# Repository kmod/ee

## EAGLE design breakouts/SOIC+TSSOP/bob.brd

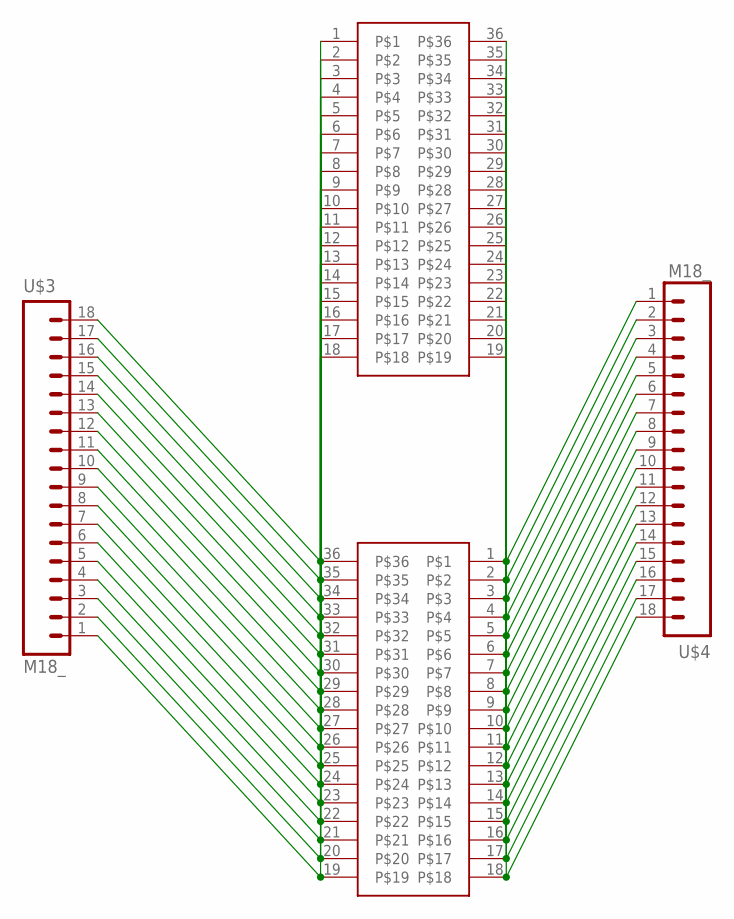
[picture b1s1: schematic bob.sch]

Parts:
U$1: 36PIN_BREAKOUTSOIC; SOIC-8-36-BREAKOUT
U$2: 36PIN_BREAKOUTTSSOP; TSSOP-8-36-BREAKOUT
U$3, U$4: M18_; 1X18

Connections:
unnamed: U$1.17, U$2.20, U$3.2
unnamed: U$1.16, U$2.21, U$3.3
unnamed: U$1.15, U$2.22, U$3.4
unnamed: U$1.14, U$2.23, U$3.5
unnamed: U$1.13, U$2.24, U$3.6
unnamed: U$1.12, U$2.25, U$3.7
unnamed: U$1.11, U$2.26, U$3.8
unnamed: U$1.10, U$2.27, U$3.9
unnamed: U$1.9, U$2.28, U$3.10
unnamed: U$1.8, U$2.29, U$3.11
unnamed: U$1.7, U$2.30, U$3.12
unnamed: U$1.6, U$2.31, U$3.13
unnamed: U$1.5, U$2.32, U$3.14
unnamed: U$1.4, U$2.33, U$3.15
unnamed: U$1.3, U$2.34, U$3.16
unnamed: U$1.2, U$2.35, U$3.17
unnamed: U$1.1, U$2.36, U$3.18
unnamed: U$1.18, U$2.19, U$3.1
unnamed: U$1.35, U$2.2, U$4.2
unnamed: U$1.34, U$2.3, U$4.3
unnamed: U$1.33, U$2.4, U$4.4
unnamed: U$1.32, U$2.5, U$4.5
unnamed: U$1.31, U$2.6, U$4.6
unnamed: U$1.30, U$2.7, U$4.7
unnamed: U$1.29, U$2.8, U$4.8
unnamed: U$1.28, U$2.9, U$4.9
unnamed: U$1.27, U$2.10, U$4.10
unnamed: U$1.26, U$2.11, U$4.11
unnamed: U$1.25, U$2.12, U$4.12
unnamed: U$1.24, U$2.13, U$4.13
unnamed: U$1.23, U$2.14, U$4.14
unnamed: U$1.22, U$2.15, U$4.15
unnamed: U$1.21, U$2.16, U$4.16
unnamed: U$1.20, U$2.17, U$4.17
unnamed: U$1.19, U$2.18, U$4.18
unnamed: U$1.36, U$2.1, U$4.1

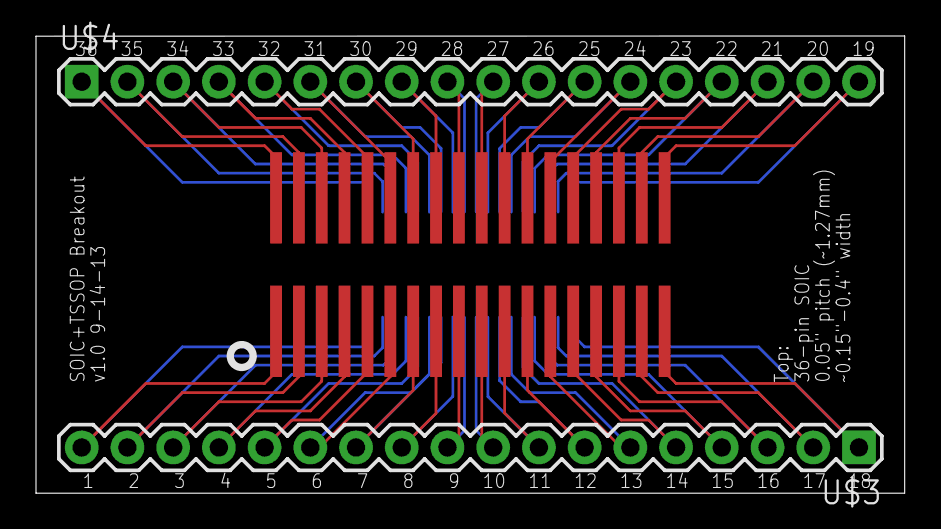
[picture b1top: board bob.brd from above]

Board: 4 copper layers, 48.3 x 25.4 mm, 4 parts (1 on the bottom side), 36 nets.

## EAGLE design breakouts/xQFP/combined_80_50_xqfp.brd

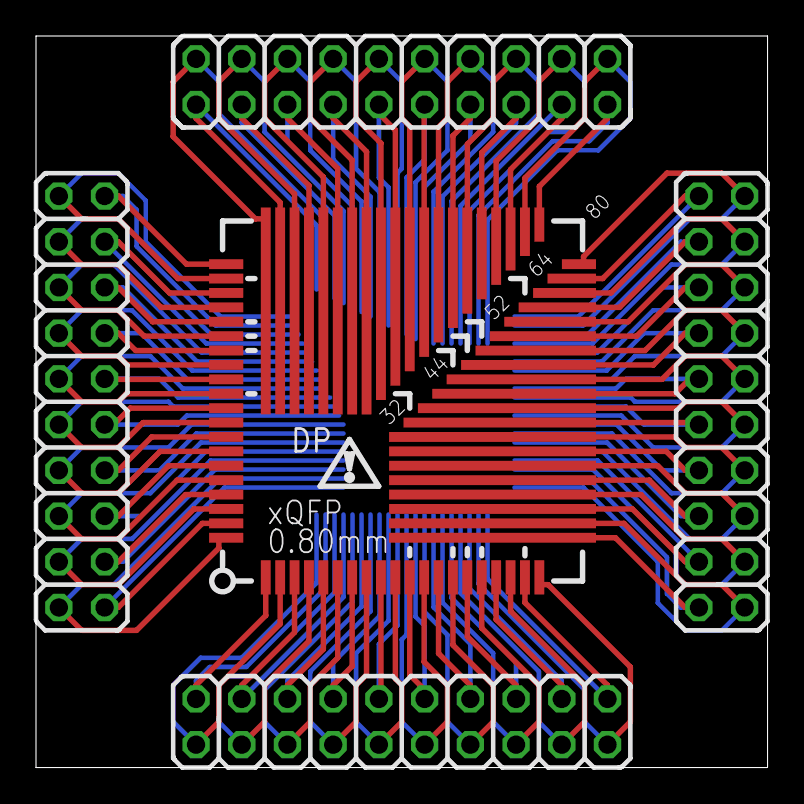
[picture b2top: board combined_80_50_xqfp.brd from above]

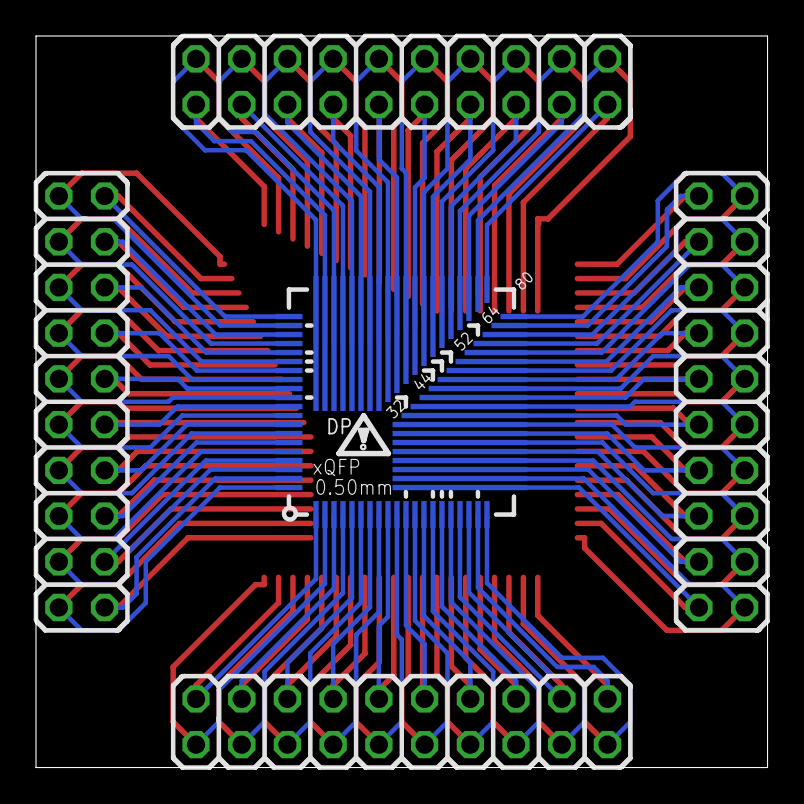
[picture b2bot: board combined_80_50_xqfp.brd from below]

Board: 4 copper layers, 40.6 x 40.6 mm, 6 parts (5 on the bottom side), 80 nets.

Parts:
JP13, JP14, JP15, JP16: 2X10
U$1: BB_XQFP_050; BB_QFP_050
U$2: BB_XQFP_080; BB_QFP_080

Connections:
unnamed: JP13.1, U$2.1
unnamed: JP13.2, U$2.2
unnamed: JP13.3, U$2.3
unnamed: JP13.4, U$2.4
unnamed: JP13.5, U$2.5
unnamed: JP13.6, U$2.6
unnamed: JP13.7, U$2.7
unnamed: JP13.8, U$2.8
unnamed: JP13.9, U$2.9
unnamed: JP13.10, U$2.10
unnamed: JP13.11, U$2.11
unnamed: JP13.12, U$2.12
unnamed: JP13.13, U$2.13
unnamed: JP13.14, U$2.14
unnamed: JP13.15, U$2.15
unnamed: JP13.16, U$2.16
unnamed: JP13.17, U$2.17
unnamed: JP13.18, U$2.18
unnamed: JP13.19, U$2.19
unnamed: JP13.20, U$2.20
unnamed: JP14.1, U$2.21
unnamed: JP14.2, U$2.22
unnamed: JP14.3, U$2.23
unnamed: JP14.4, U$2.24
unnamed: JP14.5, U$2.25
unnamed: JP14.6, U$2.26
unnamed: JP14.7, U$2.27
unnamed: JP14.8, U$2.28
unnamed: JP14.9, U$2.29
unnamed: JP14.10, U$2.30
unnamed: JP14.11, U$2.31
unnamed: JP14.12, U$2.32
unnamed: JP14.13, U$2.33
unnamed: JP14.14, U$2.34
unnamed: JP14.15, U$2.35
unnamed: JP14.16, U$2.36
unnamed: JP14.17, U$2.37
unnamed: JP14.18, U$2.38
unnamed: JP14.19, U$2.39
unnamed: JP14.20, U$2.40
unnamed: JP15.1, U$2.41
unnamed: JP15.2, U$2.42
unnamed: JP15.3, U$2.43
unnamed: JP15.4, U$2.44
unnamed: JP15.5, U$2.45
unnamed: JP15.6, U$2.46
unnamed: JP15.7, U$2.47
unnamed: JP15.8, U$2.48
unnamed: JP15.9, U$2.49
unnamed: JP15.10, U$2.50
unnamed: JP15.11, U$2.51
unnamed: JP15.12, U$2.52
unnamed: JP15.13, U$2.53
unnamed: JP15.14, U$2.54
unnamed: JP15.15, U$2.55
unnamed: JP15.16, U$2.56
unnamed: JP15.17, U$2.57
unnamed: JP15.18, U$2.58
unnamed: JP15.19, U$2.59
unnamed: JP15.20, U$2.60
unnamed: JP16.1, U$2.61
unnamed: JP16.2, U$2.62
unnamed: JP16.3, U$2.63
unnamed: JP16.4, U$2.64
unnamed: JP16.5, U$2.65
unnamed: JP16.6, U$2.66
unnamed: JP16.7, U$2.67
unnamed: JP16.8, U$2.68
unnamed: JP16.9, U$2.69
unnamed: JP16.10, U$2.70
unnamed: JP16.11, U$2.71
unnamed: JP16.12, U$2.72
unnamed: JP16.13, U$2.73
unnamed: JP16.14, U$2.74
unnamed: JP16.15, U$2.75
unnamed: JP16.16, U$2.76
unnamed: JP16.17, U$2.77
unnamed: JP16.18, U$2.78
unnamed: JP16.19, U$2.79
unnamed: JP16.20, U$2.80

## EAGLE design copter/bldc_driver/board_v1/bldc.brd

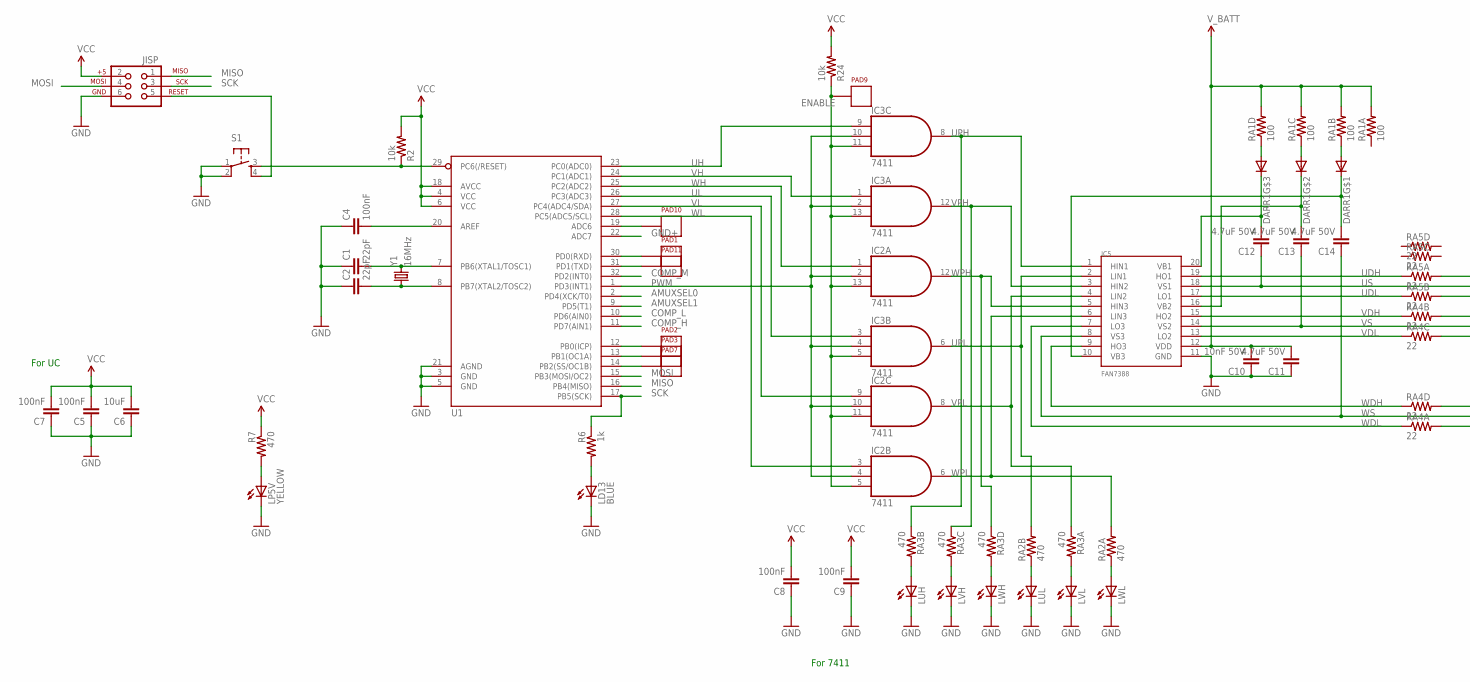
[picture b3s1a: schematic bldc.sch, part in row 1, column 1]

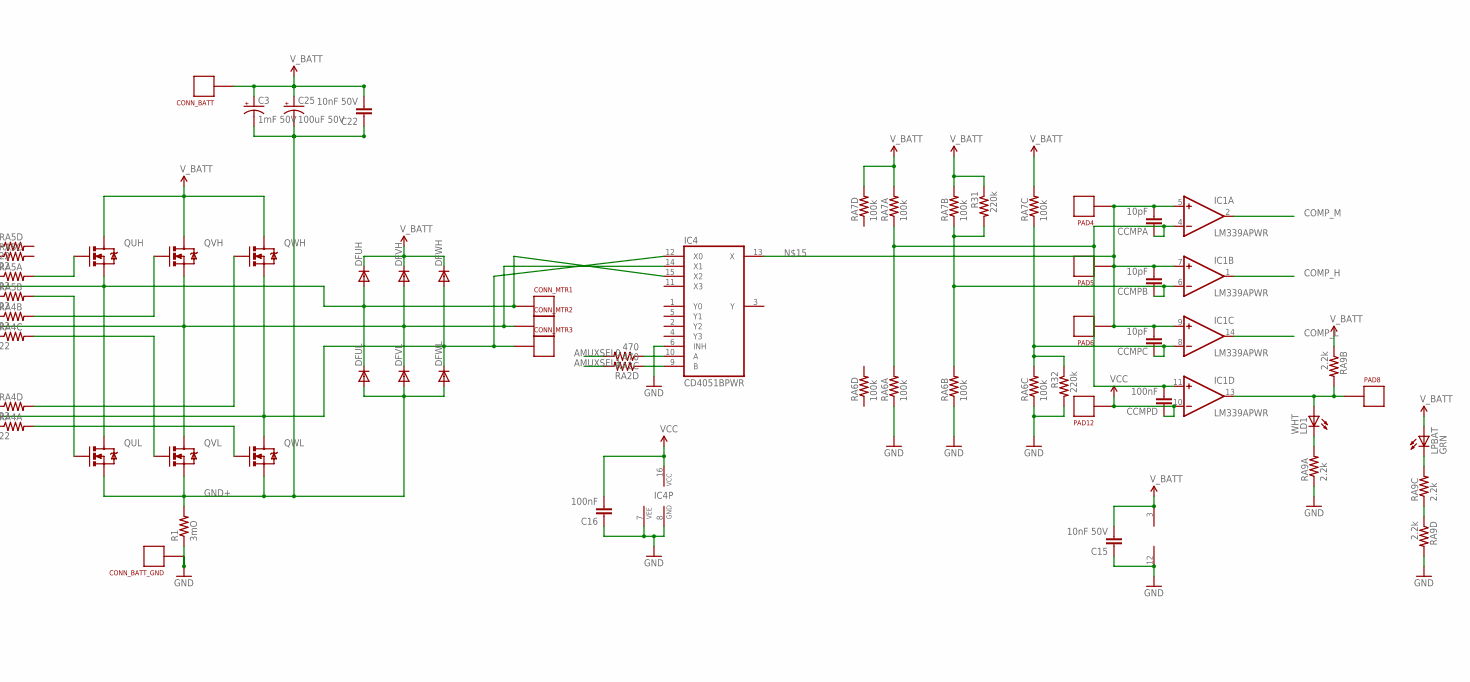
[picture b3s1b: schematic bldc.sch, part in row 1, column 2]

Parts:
C1, C2: 22pF; 0402-CAP
C3: 1mF 50V; CPOL-RADIAL-1000UF-50V
C4, C5, C7, C8, C9, C16: 100nF; 0402-CAP
C6: 10uF; 0805
C10, C15, C22: 10nF 50V; 0402-CAP
C11: 4.7uF 50V; 0805
C12, C13, C14: 4.7uF 50V; 0805; VOLTAGE 40
C25: 100uF 50V; CPOL-RADIAL-100UF-25V
CCMPA: 10pF; 0402-CAP
CCMPB: 10pF; 0402-CAP
CCMPC: 10pF; 0402-CAP
CCMPD: 100nF; 0402-CAP
CONN_BATT: CONNECTOR18AWG; HOLE_18AWG
CONN_BATT_GND: CONNECTOR18AWG; HOLE_18AWG
CONN_MTR1, CONN_MTR2, CONN_MTR3: CONNECTOR18AWG; HOLE_18AWG
DARR1: SD103ATW-7-F; SOT363
DFUH: DIODESOD123W; SOD123W(NXP)
DFUL: DIODESOD123W; SOD123W(NXP)
DFVH: DIODESOD123W; SOD123W(NXP)
DFVL: DIODESOD123W; SOD123W(NXP)
DFWH: DIODESOD123W; SOD123W(NXP)
DFWL: DIODESOD123W; SOD123W(NXP)
IC1: LM339APWR; TSSOP14
IC2, IC3: 7411; TSSOP14
IC4: CD4051BPWR; TSSOP16
IC5: FAN7388; SO20W
JISP: AVR_SPI_PRG_6PTH; 2X3
LD1: WHT; 0603_LED
LD13: BLUE; 0603_LED
LP5V: YELLOW; 0603_LED
LPBAT: GRN; 0603_LED
LUH: LED0603; 0603_LED
LUL: LED0603; 0603_LED
LVH: LED0603; 0603_LED
LVL: LED0603; 0603_LED
LWH: LED0603; 0603_LED
LWL: LED0603; 0603_LED
PAD1: PD0; TESTPAD
PAD2: PB0; TESTPAD
PAD3: PB1; TESTPAD
PAD4: CMPA; TESTPAD
PAD5: CMPB; TESTPAD
PAD6: CMPC; TESTPAD
PAD7: PB2; TESTPAD
PAD8: PGD; TESTPAD
PAD9: ENBL; TESTPAD
PAD10: ADC6; TESTPAD
PAD11: PD1; TESTPAD
PAD12: VREF; TESTPAD
QUH: NXP_LFPAK_NFET; POWERSO8
QUL: NXP_LFPAK_NFET; POWERSO8
QVH: NXP_LFPAK_NFET; POWERSO8
QVL: NXP_LFPAK_NFET; POWERSO8
QWH: NXP_LFPAK_NFET; POWERSO8
QWL: NXP_LFPAK_NFET; POWERSO8
R1: 3mO; OAR5
R2, R24: 10k; 0603-RES
R6: 1k; 0603-RES
R7: 470; 0603-RES
R31, R32: 220k; 0603-RES
RA1: 100; 0603-ARV
RA2, RA3: 470; 0603-ARV
RA4, RA5: 22; 0603-ARV
RA6, RA7: 100k; 0603-ARV
RA9: 2.2k; 0603-ARV
S1: TAC_SWITCHPTH; TACTILE-PTH
U1: ATMEGA328_SMT; TQFP32-08
Y1: 16MHz; HC49UP

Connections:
AMUXSEL0: RA2.6 (2), U1.2 (PD4(XCK/T0))
AMUXSEL1: RA2.5 (2), U1.9 (PD5(T1))
COMP_H: IC1.1 (OUT), U1.11 (PD7(AIN1))
COMP_L: IC1.14 (OUT), U1.10 (PD6(AIN0))
COMP_M: IC1.2 (OUT), U1.32 (PD2(INT0))
CTL0: PAD2.P, U1.12 (PB0(ICP))
CTL1: PAD3.P, U1.13 (PB1(OC1A))
CTL2: PAD7.P, U1.14 (PB2(SS/OC1B))
CTL3: PAD1.P, U1.30 (PD0(RXD))
ENABLE: IC2.5 (I2), IC2.11 (I2), IC2.13 (I2), IC3.5 (I2), IC3.11 (I2), IC3.13 (I2), PAD9.P, R24.1
GND: C1.1, C2.1, C4.1, C5.1, C6.1, C7.1, C8.1, C9.1, C10.1, C11.1, C15.1, C16.1, CONN_BATT_GND.P$1, IC1.12 (GND), IC2.7 (GND), IC3.7 (GND), IC4.6 (INH), IC4.7 (VEE), IC4.8 (GND), IC5.11 (GND), JISP.6, LD13.C, LP5V.C, LUH.C, LUL.C, LVH.C, LVL.C, LWH.C, LWL.C, R1.P$1 (1), R32.2, RA6.1, RA6.2 (1), RA6.3 (1), RA9.1, RA9.5 (2), S1.1, S1.2, U1.3 (GND), U1.5 (GND), U1.21 (AGND)
GND+: C3.2 (-), C22.1, C25.2 (-), DFUL.A, DFVL.A, DFWL.A, QUL.P1 (S), QUL.P2 (S), QUL.P3 (S), QVL.P1 (S), QVL.P2 (S), QVL.P3 (S), QWL.P1 (S), QWL.P2 (S), QWL.P3 (S), R1.P$2 (2), U1.22 (ADC7)
GUH: QUH.P4 (G), RA5.8 (2)
GUL: QUL.P4 (G), RA5.7 (2)
GVH: QVH.P4 (G), RA4.7 (2)
GVL: QVL.P4 (G), RA4.6 (2)
GWH: QWH.P4 (G), RA4.5 (2)
GWL: QWL.P4 (G), RA4.8 (2)
MISO: JISP.1, U1.16 (PB4(MISO))
MOSI: JISP.4, U1.15 (PB3(MOSI/OC2))
unnamed: C1.2, U1.7 (PB6(XTAL1/TOSC1)), Y1.2
unnamed: C2.2, U1.8 (PB7(XTAL2/TOSC2)), Y1.1
unnamed: CCMPA.1, CCMPD.2, IC1.4 (-IN), IC1.11 (+IN), RA6.8 (2), RA7.1
unnamed: IC1.13 (OUT), LD1.A, PAD8.P, RA9.7 (2)
unnamed: C4.2, U1.20 (AREF)
unnamed: LD13.A, R6.2
unnamed: RA9.3 (1), RA9.4 (1)
unnamed: LUH.A, RA3.7 (2)
unnamed: LWL.A, RA2.1
unnamed: LP5V.A, R7.2
unnamed: CCMPB.1, IC1.6 (-IN), R31.2, RA6.7 (2), RA7.2 (1)
unnamed: IC4.10 (A), RA2.3 (1)
unnamed: LD1.C, RA9.8 (2)
unnamed: IC4.9 (B), RA2.4 (1)
unnamed: CCMPA.2, CCMPB.2, CCMPC.2, IC1.5 (+IN), IC1.7 (+IN), IC1.9 (+IN), IC4.13 (X), PAD4.P, PAD5.P, PAD6.P
unnamed: LPBAT.C, RA9.6 (2)
unnamed: CCMPC.1, IC1.8 (-IN), R32.1, RA6.6 (2), RA7.3 (1)
unnamed: C14.2, DARR1.1 (C), IC5.10 (VB3)
unnamed: DARR1.4 (A), RA1.4 (1)
unnamed: DARR1.5 (A), RA1.3 (1)
unnamed: DARR1.6 (A), RA1.2 (1)
unnamed: JISP.5, S1.4
unnamed: LVH.A, RA3.6 (2)
unnamed: LWH.A, RA3.5 (2)
unnamed: LUL.A, RA2.2 (1)
unnamed: PAD10.P, U1.19 (ADC6)
unnamed: PAD11.P, U1.31 (PD1(TXD))
unnamed: C13.2, DARR1.2 (C), IC5.16 (VB2)
unnamed: C12.2, DARR1.3 (C), IC5.20 (VB1)
unnamed: LVL.A, RA3.8 (2)
PWM: IC2.2 (I1), IC2.4 (I1), IC2.10 (I1), IC3.2 (I1), IC3.4 (I1), IC3.10 (I1), U1.1 (PD3(INT1))
RESET: R2.1, S1.3, U1.29 (PC6(/RESET))
SCK: JISP.3, R6.1, U1.17 (PB5(SCK))
UDH: IC5.19 (HO1), RA5.1
UDL: IC5.17 (LO1), RA5.2 (1)
UH: IC3.9 (I0), U1.23 (PC0(ADC0))
UL: IC3.3 (I0), U1.26 (PC3(ADC3))
UPH: IC3.8 (O), IC5.1 (HIN1), RA3.2 (1)
UPL: IC3.6 (O), IC5.2 (LIN1), RA2.7 (2)
US: C12.1, CONN_MTR1.P$1, DFUH.A, DFUL.C, IC4.15 (X2), IC5.18 (VS1), QUH.P1 (S), QUH.P2 (S), QUH.P3 (S), QUL.P$1 (D), QUL.P$5 (D), QUL.P$6 (D), QUL.P$7 (D), QUL.P$8 (D), QUL.P$9 (D), QUL.P$10 (D), QUL.P$11 (D), QUL.P$12 (D), QUL.P$13 (D), QUL.P$14 (D), QUL.P$15 (D), QUL.P$16 (D), QUL.P$17 (D), QUL.P$19 (D), QUL.P$20 (D), QUL.P$21 (D)
VCC: C5.2, C6.2, C7.2, C8.2, C9.2, C16.2, CCMPD.1, IC1.10 (-IN), IC2.14 (VCC), IC3.14 (VCC), IC4.16 (VCC), JISP.2, PAD12.P, R2.2, R7.1, R24.2, U1.4 (VCC), U1.6 (VCC), U1.18 (AVCC)
VDH: IC5.15 (HO2), RA4.2 (1)
VDL: IC5.13 (LO2), RA4.3 (1)
VH: IC3.1 (I0), U1.24 (PC1(ADC1))
VL: IC2.9 (I0), U1.27 (PC4(ADC4/SDA))
VPH: IC3.12 (O), IC5.3 (HIN2), RA3.3 (1)
VPL: IC2.8 (O), IC5.4 (LIN2), RA3.1
VS: C13.1, CONN_MTR2.P$1, DFVH.A, DFVL.C, IC4.14 (X1), IC5.14 (VS2), QVH.P1 (S), QVH.P2 (S), QVH.P3 (S), QVL.P$1 (D), QVL.P$5 (D), QVL.P$6 (D), QVL.P$7 (D), QVL.P$8 (D), QVL.P$9 (D), QVL.P$10 (D), QVL.P$11 (D), QVL.P$12 (D), QVL.P$13 (D), QVL.P$14 (D), QVL.P$15 (D), QVL.P$16 (D), QVL.P$17 (D), QVL.P$19 (D), QVL.P$20 (D), QVL.P$21 (D)
V_BATT: C3.1 (+), C10.2, C11.2, C15.2, C22.2, C25.1 (+), CONN_BATT.P$1, DFUH.C, DFVH.C, DFWH.C, IC1.3 (V+), IC5.12 (VDD), LPBAT.A, QUH.P$1 (D), QUH.P$5 (D), QUH.P$6 (D), QUH.P$7 (D), QUH.P$8 (D), QUH.P$9 (D), QUH.P$10 (D), QUH.P$11 (D), QUH.P$12 (D), QUH.P$13 (D), QUH.P$14 (D), QUH.P$15 (D), QUH.P$16 (D), QUH.P$17 (D), QUH.P$19 (D), QUH.P$20 (D), QUH.P$21 (D), QVH.P$1 (D), QVH.P$5 (D), QVH.P$6 (D), QVH.P$7 (D), QVH.P$8 (D), QVH.P$9 (D), QVH.P$10 (D), QVH.P$11 (D), QVH.P$12 (D), QVH.P$13 (D), QVH.P$14 (D), QVH.P$15 (D), QVH.P$16 (D), QVH.P$17 (D), QVH.P$19 (D), QVH.P$20 (D), QVH.P$21 (D), QWH.P$1 (D), QWH.P$5 (D), QWH.P$6 (D), QWH.P$7 (D), QWH.P$8 (D), QWH.P$9 (D), QWH.P$10 (D), QWH.P$11 (D), QWH.P$12 (D), QWH.P$13 (D), QWH.P$14 (D), QWH.P$15 (D), QWH.P$16 (D), QWH.P$17 (D), QWH.P$19 (D), QWH.P$20 (D), QWH.P$21 (D), R31.1, RA1.5 (2), RA1.6 (2), RA1.7 (2), RA1.8 (2), RA7.5 (2), RA7.6 (2), RA7.7 (2), RA7.8 (2), RA9.2 (1)
WDH: IC5.9 (HO3), RA4.4 (1)
WDL: IC5.7 (LO3), RA4.1
WH: IC2.1 (I0), U1.25 (PC2(ADC2))
WL: IC2.3 (I0), U1.28 (PC5(ADC5/SCL))
WPH: IC2.12 (O), IC5.5 (HIN3), RA3.4 (1)
WPL: IC2.6 (O), IC5.6 (LIN3), RA2.8 (2)
WS: C14.1, CONN_MTR3.P$1, DFWH.A, DFWL.C, IC4.12 (X0), IC5.8 (VS3), QWH.P1 (S), QWH.P2 (S), QWH.P3 (S), QWL.P$1 (D), QWL.P$5 (D), QWL.P$6 (D), QWL.P$7 (D), QWL.P$8 (D), QWL.P$9 (D), QWL.P$10 (D), QWL.P$11 (D), QWL.P$12 (D), QWL.P$13 (D), QWL.P$14 (D), QWL.P$15 (D), QWL.P$16 (D), QWL.P$17 (D), QWL.P$19 (D), QWL.P$20 (D), QWL.P$21 (D)

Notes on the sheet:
For UC
For 7411

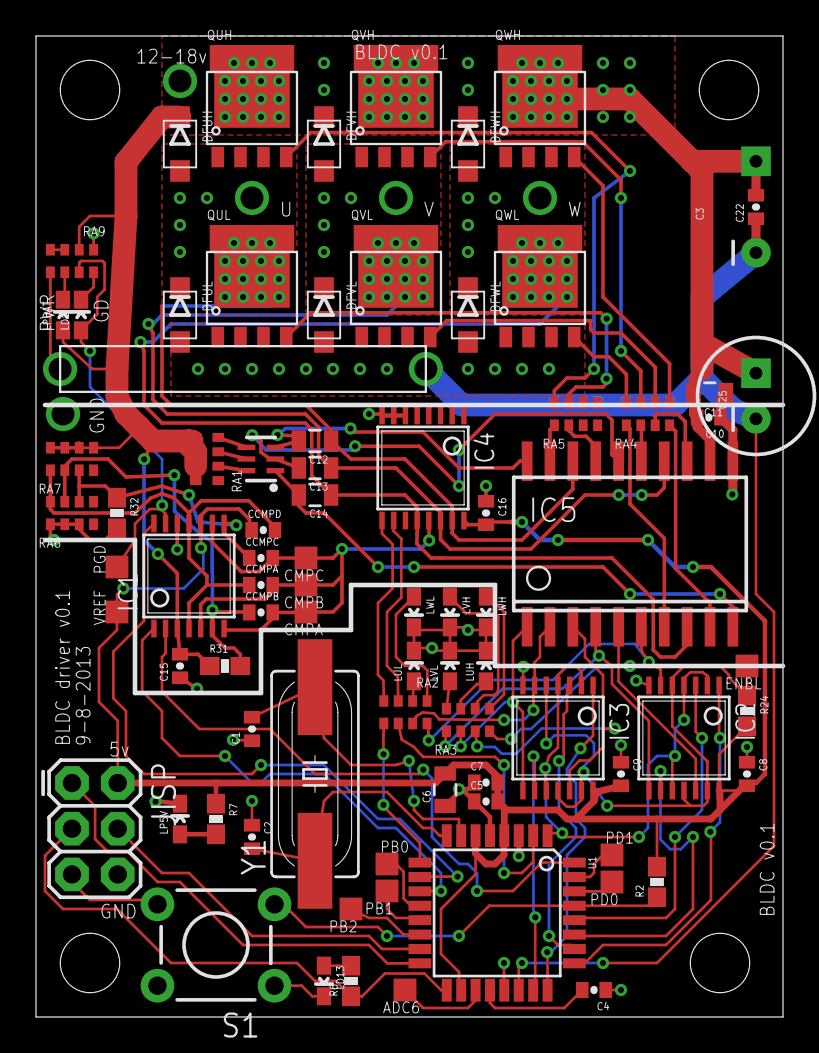
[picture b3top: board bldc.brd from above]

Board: 2 copper layers, 41.5 x 54.5 mm, 90 parts (0 on the bottom side), 76 nets.

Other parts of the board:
U$1, U$2, U$3, U$4: STAND-OFF

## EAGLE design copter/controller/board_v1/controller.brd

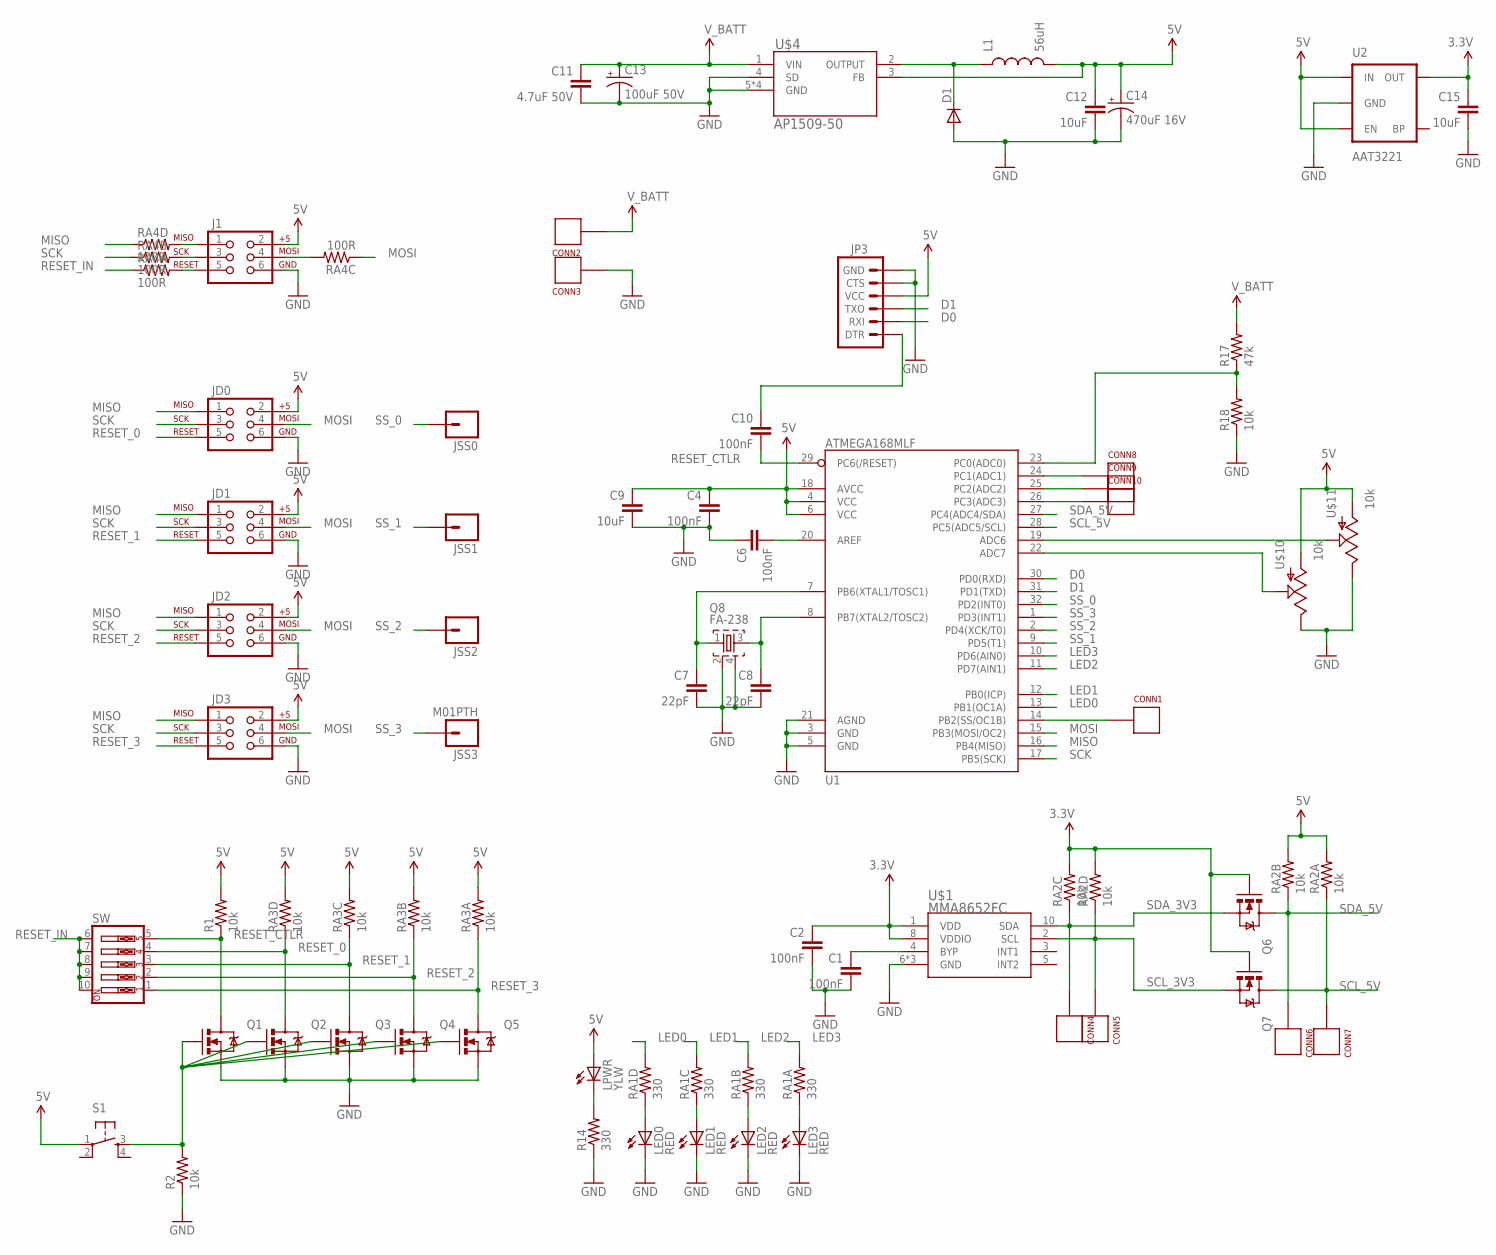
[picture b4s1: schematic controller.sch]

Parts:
C1, C2, C4, C6, C10: 100nF; 0402-CAP
C7, C8: 22pF; 0402-CAP
C9, C12, C15: 10uF; 0805
C11: 4.7uF 50V; 0805
C13: 100uF 50V; CAP-8-3.5
C14: 470uF 16V; CAP-8-3.5
CONN1: SS; TESTPAD
CONN2, CONN3: CONNECTOR18AWG; HOLE_18AWG
CONN4: D33; TESTPAD
CONN5: C33; TESTPAD
CONN6: D50; TESTPAD
CONN7: C50; TESTPAD
CONN8: PC1; TESTPAD
CONN9: PC2; TESTPAD
CONN10: PC3; TESTPAD
D1: DIODESOD123W; SOD123W(NXP)
J1: AVR_SPI_PRG_6PTH; 2X3
JD0, JD1, JD2, JD3: AVR_SPI_PRG_6PTH; 2X3
JP3: ARDUINO_SERIAL_PROGRAMPTH; 1X06
JSS0, JSS1, JSS2, JSS3: M01PTH; 1X01
L1: 56uH; 1210
LED0, LED1, LED2, LED3: RED; LED-0603
LPWR: YLW; LED-0603
Q1, Q2, Q3, Q4, Q5, Q6, Q7: MOSFET-NCHANNELBSS123LT1G; SOT23
Q8: FA-238
R1, R2, R18: 10k; 0603-RES
R14: 330; 0603-RES
R17: 47k; 0603-RES
RA1: 330; 0603-ARV
RA2, RA3: 10k; 0603-ARV
RA4: 100R; 0603-ARV
S1: TAC_SWITCHPTH; TACTILE-PTH
SW: SW_DIP-5; DIPSWITCH-05
U1: ATMEGA168MLF; MLF32
U2: AAT3221; SOT23-5
U$1: MMA8652FC; DFN-10
U$4: AP1509-50; SO08
U$10, U$11: 10k; TRIM_POT

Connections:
3.3V: C2.1, C15.1, Q6.1 (G), Q7.1 (G), RA2.5 (2), RA2.6 (2), U2.5 (OUT), U$1.1 (VDD), U$1.8 (VDDIO)
5V: C4.1, C9.1, C12.1, C14.1 (+), J1.2, JD0.2, JD1.2, JD2.2, JD3.2, JP3.4 (VCC), L1.2, LPWR.A, R1.2, RA2.7 (2), RA2.8 (2), RA3.5 (2), RA3.6 (2), RA3.7 (2), RA3.8 (2), S1.1, U1.4 (VCC), U1.6 (VCC), U1.18 (AVCC), U2.1 (IN), U2.3 (EN), U$4.3 (FB), U$10.3 (A), U$11.3 (A)
D0: JP3.2 (RXI), U1.30 (PD0(RXD))
D1: JP3.3 (TXO), U1.31 (PD1(TXD))
GND: C1.2, C2.2, C4.2, C6.1, C7.2, C8.2, C9.2, C11.2, C12.2, C13.2 (-), C14.2 (-), C15.2, CONN3.P$1, D1.A, J1.6, JD0.6, JD1.6, JD2.6, JD3.6, JP3.5 (CTS), JP3.6 (GND), LED0.C, LED1.C, LED2.C, LED3.C, Q1.2 (S), Q2.2 (S), Q3.2 (S), Q4.2 (S), Q5.2 (S), Q8.2, Q8.4, R2.1, R14.1, R18.1, U1.3 (GND), U1.5 (GND), U1.21 (AGND), U2.2 (GND), U$1.6 (GND), U$1.7 (GND), U$1.9 (GND), U$4.4 (SD), U$4.5 (GND), U$4.6 (GND), U$4.7 (GND), U$4.8 (GND), U$10.2 (E), U$11.2 (E)
LED0: RA1.5 (2), U1.13 (PB1(OC1A))
LED1: RA1.6 (2), U1.12 (PB0(ICP))
LED2: RA1.7 (2), U1.11 (PD7(AIN1))
LED3: RA1.8 (2), U1.10 (PD6(AIN0))
MISO: JD0.1, JD1.1, JD2.1, JD3.1, RA4.4 (1), U1.16 (PB4(MISO))
MOSI: JD0.4, JD1.4, JD2.4, JD3.4, RA4.3 (1), U1.15 (PB3(MOSI/OC2))
unnamed: Q1.1 (G), Q2.1 (G), Q3.1 (G), Q4.1 (G), Q5.1 (G), R2.2, S1.3
unnamed: C8.1, Q8.3, U1.8 (PB7(XTAL2/TOSC2))
unnamed: C1.1, U$1.4 (BYP)
unnamed: C6.2, U1.20 (AREF)
unnamed: C7.1, Q8.1, U1.7 (PB6(XTAL1/TOSC1))
unnamed: CONN1.P, U1.14 (PB2(SS/OC1B))
unnamed: LPWR.C, R14.2
unnamed: J1.5, RA4.8 (2)
unnamed: J1.4, RA4.6 (2)
unnamed: J1.1, RA4.5 (2)
unnamed: LED0.A, RA1.4 (1)
unnamed: R17.1, R18.2, U1.23 (PC0(ADC0))
unnamed: LED1.A, RA1.3 (1)
unnamed: C10.1, JP3.1 (DTR)
unnamed: J1.3, RA4.7 (2)
unnamed: LED2.A, RA1.2 (1)
unnamed: CONN8.P, U1.24 (PC1(ADC1))
unnamed: U1.19 (ADC6), U$11.1 (S)
unnamed: U1.22 (ADC7), U$10.1 (S)
unnamed: CONN9.P, U1.25 (PC2(ADC2))
unnamed: CONN10.P, U1.26 (PC3(ADC3))
unnamed: LED3.A, RA1.1
unnamed: D1.C, L1.1, U$4.2 (OUTPUT)
RESET_0: JD0.5, Q2.3 (D), RA3.4 (1), SW.4
RESET_1: JD1.5, Q3.3 (D), RA3.3 (1), SW.3
RESET_2: JD2.5, Q4.3 (D), RA3.2 (1), SW.2
RESET_3: JD3.5, Q5.3 (D), RA3.1, SW.1
RESET_CTLR: C10.2, Q1.3 (D), R1.1, SW.5, U1.29 (PC6(/RESET))
RESET_IN: RA4.1, SW.6 (12), SW.7 (13), SW.8 (14), SW.9 (15), SW.10 (16)
SCK: JD0.3, JD1.3, JD2.3, JD3.3, RA4.2 (1), U1.17 (PB5(SCK))
SCL_3V3: CONN5.P, Q7.2 (S), RA2.4 (1), U$1.2 (SCL)
SCL_5V: CONN7.P, Q7.3 (D), RA2.1, U1.28 (PC5(ADC5/SCL))
SDA_3V3: CONN4.P, Q6.2 (S), RA2.3 (1), U$1.10 (SDA)
SDA_5V: CONN6.P, Q6.3 (D), RA2.2 (1), U1.27 (PC4(ADC4/SDA))
SS_0: JSS0.1, U1.32 (PD2(INT0))
SS_1: JSS1.1, U1.9 (PD5(T1))
SS_2: JSS2.1, U1.2 (PD4(XCK/T0))
SS_3: JSS3.1, U1.1 (PD3(INT1))
V_BATT: C11.1, C13.1 (+), CONN2.P$1, R17.2, U$4.1 (VIN)

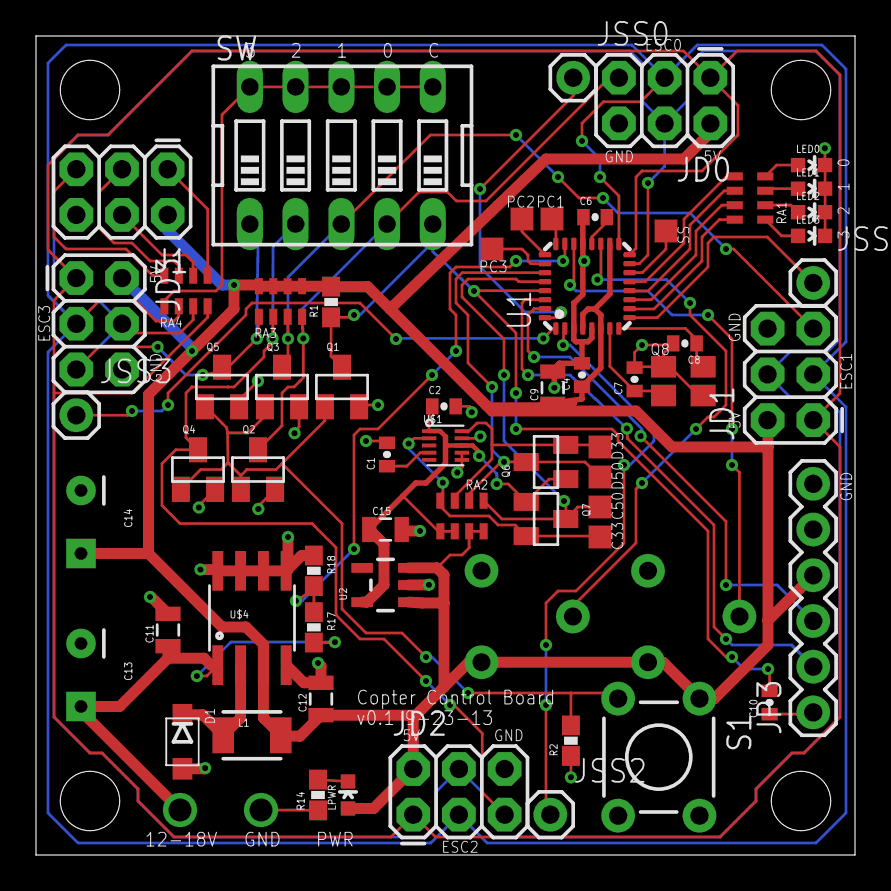
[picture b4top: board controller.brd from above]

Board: 2 copper layers, 45.5 x 45.5 mm, 69 parts (0 on the bottom side), 50 nets.

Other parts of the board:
U$5, U$6, U$7, U$8: STAND-OFF

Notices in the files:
parts and their libraries:
SparkFun-Connectors: Licensing: CC v3.0 Share-Alike You are welcome to use this library for commercial purposes.
SparkFun-Connectors: Licensing: Creative Commons ShareAlike 4.0 International - https://creativecommons.org/licenses/by-sa/4.0
